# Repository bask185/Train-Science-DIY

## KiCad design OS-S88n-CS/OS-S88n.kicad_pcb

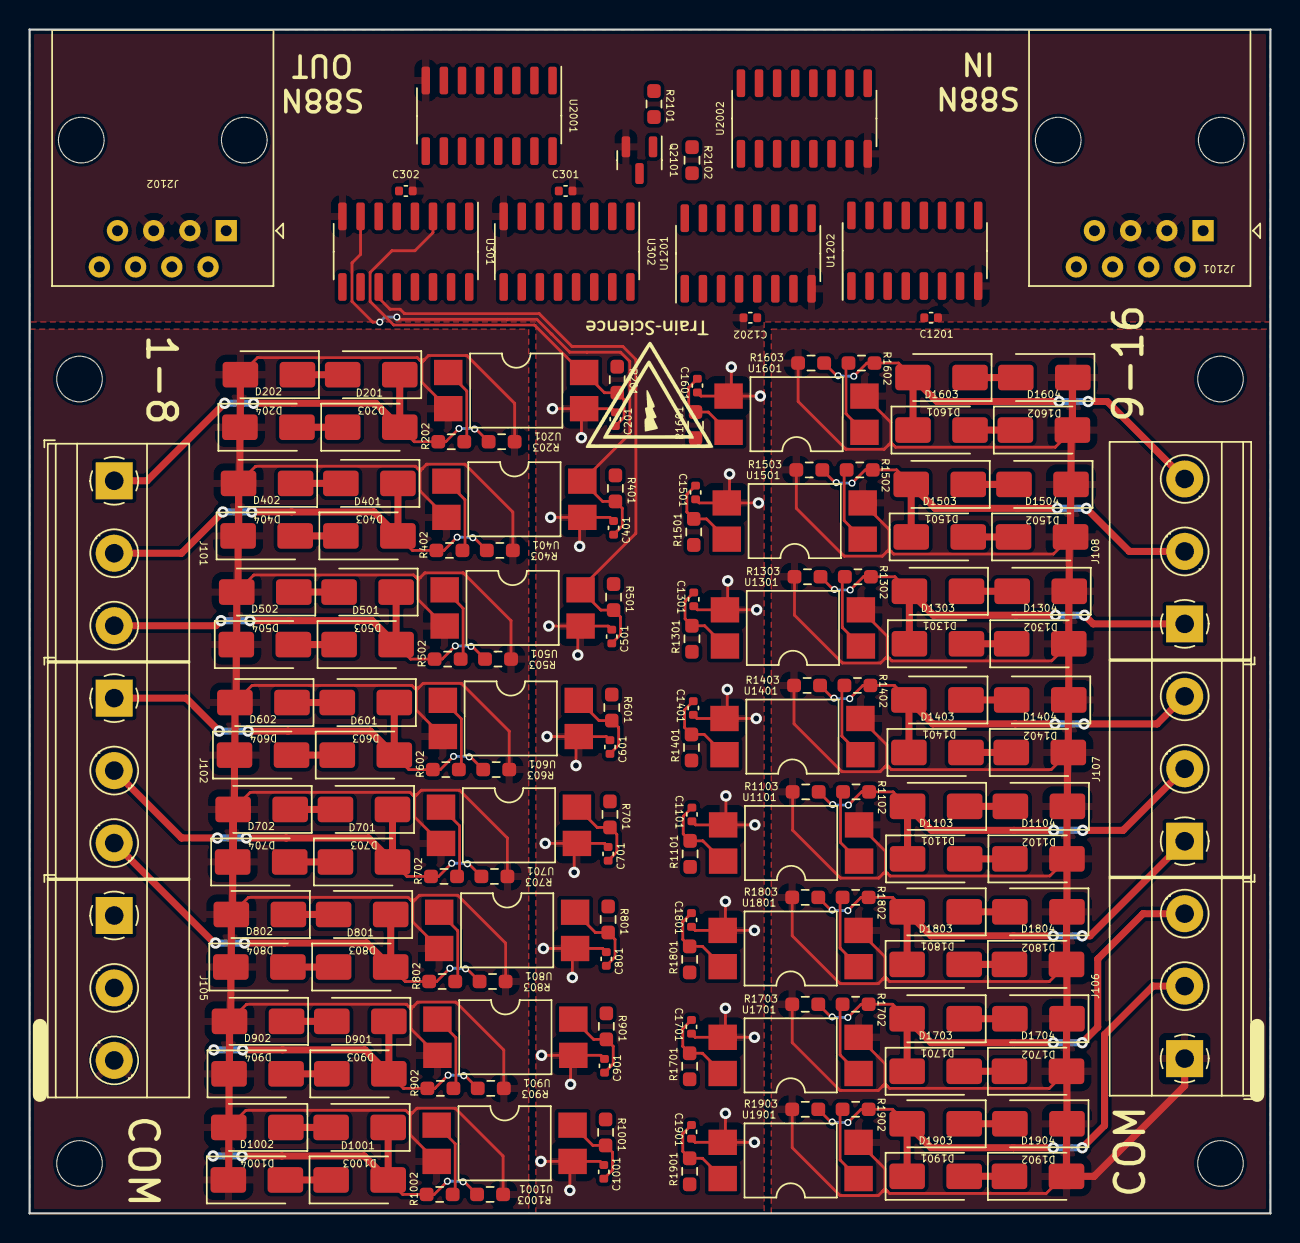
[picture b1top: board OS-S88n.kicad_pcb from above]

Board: 2 copper layers, 87.0 x 83.0 mm, 165 parts (0 on the bottom side), 107 nets.

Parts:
C201, C301, C302, C401, C501, C601, C701, C801, C901, C1001, C1101, C1201, C1202, C1301, C1401, C1501, C1601, C1701, C1801, C1901: 100nF; C_0402_1005Metric
D201, D202, D203, D204, D401, D402, D403, D404, D501, D502, D503, D504, D601, D602, D603, D604, D701, D702, D703, D704, D801, D802, D803, D804, D901, D902, D903, D904, D1001, D1002, D1003, D1004, D1101, D1102, D1103, D1104, D1301, D1302, D1303, D1304, D1401, D1402, D1403, D1404, D1501, D1502, D1503, D1504, D1601, D1602, D1603, D1604, D1701, D1702, D1703, D1704, D1801, D1802, D1803, D1804, D1901, D1902, D1903, D1904: SS53; D_SMA
J101, J102, J105, J106, J107, J108: Screw_Terminal_01x03; TerminalBlock_Phoenix_MKDS-1,5-3-5.08_1x03_P5.08mm_Horizont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
J2101, J2102: RJ45; RJ45_Amphenol_54602-x08_Horizontal
Q2101: BC847; SOT-23
R201, R401, R501, R601, R701, R801, R901, R1001, R1101, R1301, R1401, R1501, R1601, R1701, R1801, R1901: 10k; R_0603_smalltext
R202, R402, R502, R602, R702, R802, R902, R1002, R1102, R1302, R1402, R1502, R1602, R1702, R1802, R1902: 47R; R_0603_smalltext
R203, R403, R503, R603, R703, R803, R903, R1003, R1103, R1303, R1403, R1503, R1603, R1703, R1803, R1903, R2101: 4k7; R_0603_smalltext
R2102: 100k; R_0603_smalltext
U201, U401, U501, U601, U701, U801, U901, U1001, U1101, U1301, U1401, U1501, U1601, U1701, U1801, U1901: EL814; SMDIP-4_W9.53mm
U301, U302, U1201, U1202: SOIC-16_3.9x9.9mm_P1.27mm
U2001, U2002: 4014; SOIC-16_3.9x9.9mm_P1.27mm

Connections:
/CS1/CMOS: C201.1, R201.2, U201.4, U301.3 (S1)
/CS1/TRACK: D201.2 (A), D203.1 (K), J101.1, R202.1, R203.1
/CS2/CMOS: C401.1, R401.2, U301.7 (S2), U401.4
/CS2/TRACK: D401.2 (A), D403.1 (K), J101.2, R402.1, R403.1
/CS3/CMOS: C501.1, R501.2, U301.11 (S3), U501.4
/CS3/TRACK: D501.2 (A), D503.1 (K), J101.3, R502.1, R503.1
/CS4/CMOS: C601.1, R601.2, U301.15 (S4), U601.4
/CS4/TRACK: D601.2 (A), D603.1 (K), J102.1, R602.1, R603.1
/CS5/CMOS: C701.1, R701.2, U302.3 (S1), U701.4
/CS5/TRACK: D701.2 (A), D703.1 (K), J102.2, R702.1, R703.1
/CS6/CMOS: C801.1, R801.2, U302.7 (S2), U801.4
/CS6/TRACK: D801.2 (A), D803.1 (K), J102.3, R802.1, R803.1
/CS7/CMOS: C901.1, R901.2, U302.11 (S3), U901.4
/CS7/TRACK: D901.2 (A), D903.1 (K), J105.1, R902.1, R903.1
/CS8/CMOS: C1001.1, R1001.2, U302.15 (S4), U1001.4
/CS8/TRACK: D1001.2 (A), D1003.1 (K), J105.2, R1002.1, R1003.1
/CS9/CMOS: C1901.1, R1901.2, U1201.3 (S1), U1901.4
/CS9/TRACK: D1901.2 (A), D1903.1 (K), J106.2, R1902.1, R1903.1
/CS10/CMOS: C1701.1, R1701.2, U1201.7 (S2), U1701.4
/CS10/TRACK: D1701.2 (A), D1703.1 (K), J106.3, R1702.1, R1703.1
/CS11/CMOS: C1801.1, R1801.2, U1201.11 (S3), U1801.4
/CS11/TRACK: D1801.2 (A), D1803.1 (K), J107.1, R1802.1, R1803.1
/CS12/CMOS: C1101.1, R1101.2, U1101.4, U1201.15 (S4)
/CS12/TRACK: D1101.2 (A), D1103.1 (K), J107.2, R1102.1, R1103.1
/CS13/CMOS: C1401.1, R1401.2, U1202.3 (S1), U1401.4
/CS13/TRACK: D1401.2 (A), D1403.1 (K), J107.3, R1402.1, R1403.1
/CS14/CMOS: C1301.1, R1301.2, U1202.7 (S2), U1301.4
/CS14/TRACK: D1301.2 (A), D1303.1 (K), J108.1, R1302.1, R1303.1
/CS15/CMOS: C1501.1, R1501.2, U1202.11 (S3), U1501.4
/CS15/TRACK: D1501.2 (A), D1503.1 (K), J108.2, R1502.1, R1503.1
/CS16/CMOS: C1601.1, R1601.2, U1202.15 (S4), U1601.4
/CS16/TRACK: D1601.2 (A), D1603.1 (K), J108.3, R1602.1, R1603.1
/RJ45/CLOCK: J2101.4, J2102.4, U2001.10 (CP), U2002.10 (CP)
/RJ45/DATA_IN: J2101.2, U2001.11 (DS)
/RJ45/DATA_OUT: J2102.2, U2002.3 (Q7)
/RJ45/PL: J2101.6, J2102.6, U2001.9 (PL), U2002.9 (PL)
/RJ45/RESET: Q2101.3 (C), R2102.2, U301.4 (R1), U301.6 (R2), U301.12 (R3), U301.14 (R4), U302.4 (R1), U302.6 (R2), U302.12 (R3), U302.14 (R4), U1201.4 (R1), U1201.6 (R2), U1201.12 (R3), U1201.14 (R4), U1202.4 (R1), U1202.6 (R2), U1202.12 (R3), U1202.14 (R4)
/SR-latch1/Q1: U301.13 (Q1), U2001.7 (P0)
/SR-latch1/Q2: U301.9 (Q2), U2001.6 (P1)
/SR-latch1/Q3: U301.10 (Q3), U2001.5 (P2)
/SR-latch1/Q4: U301.1 (Q4), U2001.4 (P3)
/SR-latch1/Q5: U302.13 (Q1), U2001.13 (P4)
/SR-latch1/Q6: U302.9 (Q2), U2001.14 (P5)
/SR-latch1/Q7: U302.10 (Q3), U2001.15 (P6)
/SR-latch1/Q8: U302.1 (Q4), U2001.1 (P7)
/SR-latch2/Q1: U1201.13 (Q1), U2002.7 (P0)
/SR-latch2/Q2: U1201.9 (Q2), U2002.6 (P1)
/SR-latch2/Q3: U1201.10 (Q3), U2002.5 (P2)
/SR-latch2/Q4: U1201.1 (Q4), U2002.4 (P3)
/SR-latch2/Q5: U1202.13 (Q1), U2002.13 (P4)
/SR-latch2/Q6: U1202.9 (Q2), U2002.14 (P5)
/SR-latch2/Q7: U1202.10 (Q3), U2002.15 (P6)
/SR-latch2/Q8: U1202.1 (Q4), U2002.1 (P7)
COM: D202.1 (K), D204.2 (A), D402.1 (K), D404.2 (A), D502.1 (K), D504.2 (A), D602.1 (K), D604.2 (A), D702.1 (K), D704.2 (A), D802.1 (K), D804.2 (A), D902.1 (K), D904.2 (A), D1002.1 (K), D1004.2 (A), D1102.1 (K), D1104.2 (A), D1302.1 (K), D1304.2 (A), D1402.1 (K), D1404.2 (A), D1502.1 (K), D1504.2 (A), D1602.1 (K), D1604.2 (A), D1702.1 (K), D1704.2 (A), D1802.1 (K), D1804.2 (A), D1902.1 (K), D1904.2 (A), J105.3, J106.1, R203.2, R403.2, R503.2, R603.2, R703.2, R803.2, R903.2, R1003.2, R1103.2, R1303.2, R1403.2, R1503.2, R1603.2, R1703.2, R1803.2, R1903.2, U201.2, U401.2, U501.2, U601.2, U701.2, U801.2, U901.2, U1001.2, U1101.2, U1301.2, U1401.2, U1501.2, U1601.2, U1701.2, U1801.2, U1901.2
GND: C201.2, C301.2, C302.2, C401.2, C501.2, C601.2, C701.2, C801.2, C901.2, C1001.2, C1101.2, C1201.2, C1202.2, C1301.2, C1401.2, C1501.2, C1601.2, C1701.2, C1801.2, C1901.2, J2101.3, J2101.5, J2102.3, J2102.5, Q2101.2 (E), U201.3, U301.8 (GND), U302.8 (GND), U401.3, U501.3, U601.3, U701.3, U801.3, U901.3, U1001.3, U1101.3, U1201.8 (GND), U1202.8 (GND), U1301.3, U1401.3, U1501.3, U1601.3, U1701.3, U1801.3, U1901.3, U2001.8 (Vss), U2002.8 (Vss)
unnamed: D201.1 (K), D202.2 (A)
unnamed: D203.2 (A), D204.1 (K)
unnamed: D401.1 (K), D402.2 (A)
unnamed: D403.2 (A), D404.1 (K)
unnamed: D501.1 (K), D502.2 (A)
unnamed: D503.2 (A), D504.1 (K)
unnamed: D601.1 (K), D602.2 (A)
unnamed: D603.2 (A), D604.1 (K)
unnamed: D701.1 (K), D702.2 (A)
unnamed: D703.2 (A), D704.1 (K)
unnamed: D801.1 (K), D802.2 (A)
unnamed: D803.2 (A), D804.1 (K)
unnamed: D901.1 (K), D902.2 (A)
unnamed: D903.2 (A), D904.1 (K)
unnamed: D1001.1 (K), D1002.2 (A)
unnamed: D1003.2 (A), D1004.1 (K)
unnamed: D1101.1 (K), D1102.2 (A)
unnamed: D1103.2 (A), D1104.1 (K)
unnamed: D1301.1 (K), D1302.2 (A)
unnamed: D1303.2 (A), D1304.1 (K)
unnamed: D1401.1 (K), D1402.2 (A)
unnamed: D1403.2 (A), D1404.1 (K)
unnamed: D1501.1 (K), D1502.2 (A)
unnamed: D1503.2 (A), D1504.1 (K)
unnamed: D1601.1 (K), D1602.2 (A)
unnamed: D1603.2 (A), D1604.1 (K)
unnamed: D1701.1 (K), D1702.2 (A)
unnamed: D1703.2 (A), D1704.1 (K)
unnamed: D1801.1 (K), D1802.2 (A)
unnamed: D1803.2 (A), D1804.1 (K)
unnamed: D1901.1 (K), D1902.2 (A)
unnamed: D1903.2 (A), D1904.1 (K)
unnamed: J2101.7, J2102.7, R2101.1
unnamed: Q2101.1 (B), R2101.2
unnamed: R202.2, U201.1
unnamed: R402.2, U401.1
unnamed: R502.2, U501.1
unnamed: R602.2, U601.1
unnamed: R702.2, U701.1
unnamed: R802.2, U801.1
unnamed: R902.2, U901.1
unnamed: R1002.2, U1001.1
unnamed: R1102.2, U1101.1
unnamed: R1302.2, U1301.1
unnamed: R1402.2, U1401.1
unnamed: R1502.2, U1501.1
unnamed: R1602.2, U1601.1
unnamed: R1702.2, U1701.1
unnamed: R1802.2, U1801.1
unnamed: R1902.2, U1901.1
unnamed: U2001.3 (Q7), U2002.11 (DS)
VCC: C301.1, C302.1, C1201.1, C1202.1, J2101.1, J2102.1, R201.1, R401.1, R501.1, R601.1, R701.1, R801.1, R901.1, R1001.1, R1101.1, R1301.1, R1401.1, R1501.1, R1601.1, R1701.1, R1801.1, R1901.1, R2102.1, U301.5 (enable), U302.5 (enable), U1201.5 (enable), U1202.5 (enable), U2001.16 (Vdd), U2002.16 (Vdd)

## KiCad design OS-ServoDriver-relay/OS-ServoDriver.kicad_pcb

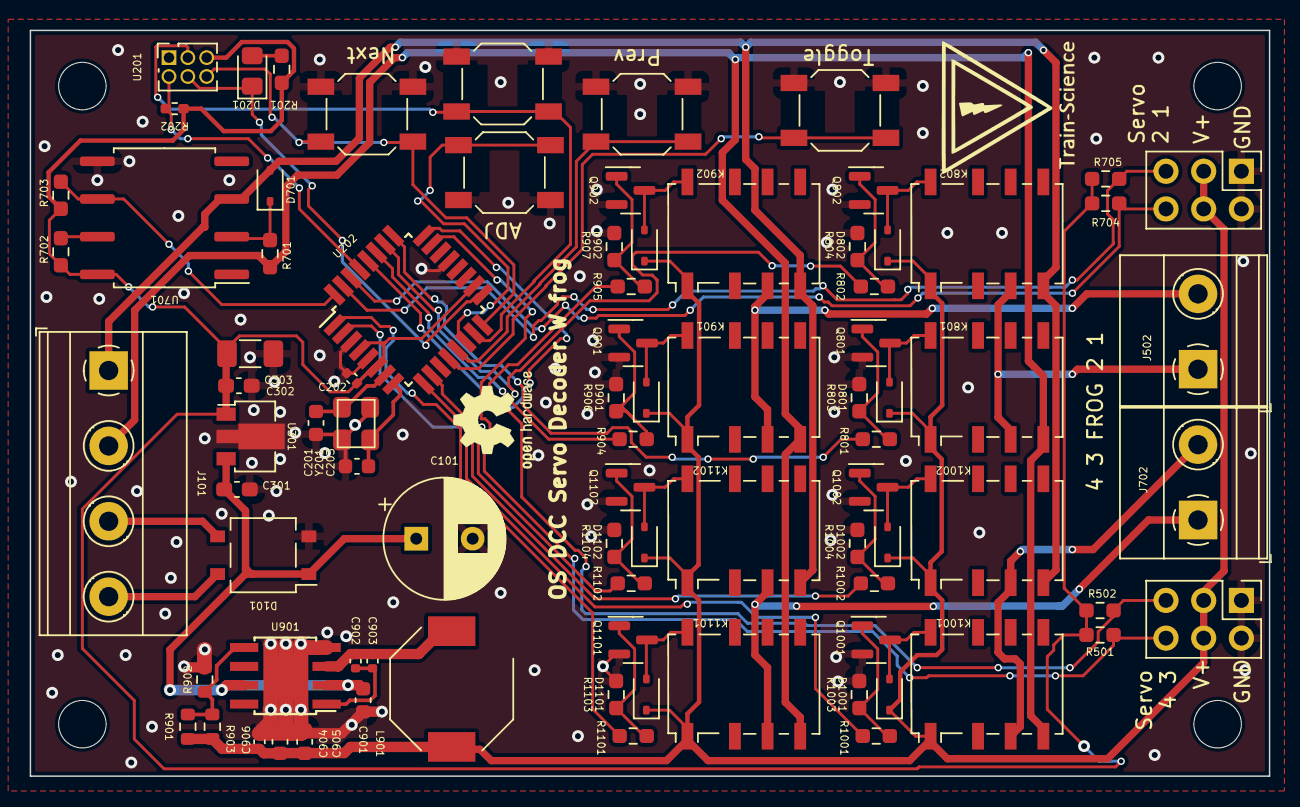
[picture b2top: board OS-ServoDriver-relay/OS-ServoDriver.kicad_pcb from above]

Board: 2 copper layers, 83.5 x 50.2 mm, 85 parts (0 on the bottom side), 56 nets.

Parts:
C101: 100uF; CP_Radial_D8.0mm_P3.80mm
C201, C203: 12pF; C_0603_1608Metric
C202, C902, C906: 100nF; C_0402_1005Metric
C301: 330nF; C_0603_1608Metric_Pad1.08x0.95mm_HandSolder
C302: 100nF; C_0603_1608Metric_Pad1.08x0.95mm_HandSolder
C303: 100uF; C_1206_3216Metric_Pad1.33x1.80mm_HandSolder
C901, C904, C905: 22uF; C_0603_1608Metric
C903: 22nF; C_0402_1005Metric
D101: MB10S; TO-269AA
D201: LED; LED_0805_2012Metric_Pad1.15x1.40mm_HandSolder
D701, D801, D802, D901, D902, D1001, D1002, D1101, D1102: 1N4148WS; D_SOD-323
J101: Screw_Terminal_01x04; TerminalBlock_Phoenix_MKDS-1,5-4-5.08_1x04_P5.08mm_Horizont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
J501, J701: Servo; PinHeader_2x03_P2.54mm_Vertical
J502, J702: Frogs; TerminalBlock_Phoenix_MKDS-1,5-2-5.08_1x02_P5.08mm_Horizont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
K801, K802, K901, K902, K1001, K1002, K1101, K1102: G6K-2F-Y-TR DC5; Relay_DPDT_Omron_G6K-2F-Y
L901: L; L_Bourns-SRU8028_8.0x8.0mm
Q801, Q802, Q901, Q902, Q1001, Q1002, Q1101, Q1102: AO3400A; SOT-23
R201: 6k2; R_0603_1608Metric_Pad0.98x0.95mm_HandSolder
R202: 10k; R_0402_1005Metric_Pad0.72x0.64mm_HandSolder
R501, R502, R702, R703, R704, R705, R803, R804, R906, R907, R1003, R1004, R1103, R1104: 10k; R_0603_smalltext
R701: 1k5; R_0603_smalltext
R801, R802, R904, R905, R1001, R1002, R1101, R1102: 22R; R_0603_smalltext
R901: 220k; R_0603_1608Metric
R902: 20k; R_0603_1608Metric
R903: 150k; R_0603_1608Metric
SW101, SW102, SW103, SW104, SW105: default_switch
U201: HEADER_3x2; PinSocket_2x03_P1.27mm_Vertical
U202: ATmega328-A; TQFP-32_7x7mm_P0.8mm
U301: L78L05_SOT89; SOT-89-3
U701: 6N137; SOP-8_6.62x9.15mm_P2.54mm
U901: MT2499A; TI_SO-PowerPAD-8
Y201: Crystal_GND2; crystal_arduino

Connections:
+5V: C202.1, C302.1, C303.1, R201.1, R202.1, R501.1, R502.1, R702.1, R703.1, R704.1, R705.1, U201.5, U202.4 (VCC), U202.6 (VCC), U202.18 (AVCC), U301.1 (OUT), U701.8 (VCC)
+5VA: C904.1, C905.1, C906.1, D801.1 (K), D802.1 (K), D901.1 (K), D902.1 (K), D1001.1 (K), D1002.1 (K), D1101.1 (K), D1102.1 (K), J501.3, J501.4, J701.3, J701.4, K801.1, K802.1, K901.1, K902.1, K1001.1, K1002.1, K1101.1, K1102.1, L901.2, R901.1, R903.2
/DCC/DCC_TTL: R703.2, U202.32 (PD2), U701.6 (VO)
/DCC_A: J101.2, K801.4, K901.4, K1001.4, K1101.4, R701.1
/DCC_B: D701.2 (A), J101.1, K802.4, K902.4, K1002.4, K1102.4, U701.3 (C)
/Servo1-2/Frog1: J502.1, K801.3, K802.3
/Servo1-2/Frog2: J502.2, K901.3, K902.3
/Servo1-2/Relay1: R801.1, U202.25 (PC2)
/Servo1-2/Relay2: R802.1, U202.26 (PC3)
/Servo1-2/Relay3: R904.1, U202.27 (PC4)
/Servo1-2/Relay4: R905.1, U202.28 (PC5)
/Servo1-2/Servo1: J501.6, R501.2, U202.23 (PC0)
/Servo1-2/Servo2: J501.5, R502.2, U202.24 (PC1)
/Servo3-4/Frog1: J702.1, K1101.3, K1102.3
/Servo3-4/Frog2: J702.2, K1001.3, K1002.3
/Servo3-4/Relay1: R1101.1, U202.1 (PD3)
/Servo3-4/Relay2: R1102.1, U202.2 (PD4)
/Servo3-4/Relay3: R1001.1, U202.9 (PD5)
/Servo3-4/Relay4: R1002.1, U202.10 (PD6)
/Servo3-4/Servo1: J701.6, R704.2, U202.30 (PD0)
/Servo3-4/Servo2: J701.5, R705.2, U202.31 (PD1)
/atmega/D8: SW105.2 (B), U202.12 (PB0)
/atmega/D9: SW104.2 (B), U202.13 (PB1)
/atmega/D10: SW103.2 (B), U202.14 (PB2)
/atmega/LED: D201.1 (K), U201.4, U202.17 (PB5)
/atmega/MISO: SW101.2 (B), U201.6, U202.16 (PB4)
/atmega/MOSI: SW102.2 (B), U201.3, U202.15 (PB3)
/atmega/X1: C201.2, U202.7 (XTAL1/PB6), Y201.1
/atmega/X2: C203.2, U202.8 (XTAL2/PB7), Y201.3
/atmega/reset: R202.2, U201.2, U202.29 (~RESET/PC6)
GND: C101.2, C201.1, C202.2, C203.1, C301.2, C302.2, C303.2, C901.2, C904.2, C905.2, C906.2, D101.2 (-), J501.1, J501.2, J701.1, J701.2, Q801.2 (S), Q802.2 (S), Q901.2 (S), Q902.2 (S), Q1001.2 (S), Q1002.2 (S), Q1101.2 (S), Q1102.2 (S), R803.1, R804.1, R902.2, R906.1, R907.1, R1003.1, R1004.1, R1103.1, R1104.1, SW101.1 (A), SW102.1 (A), SW103.1 (A), SW104.1 (A), SW105.1 (A), U201.1, U202.3 (GND), U202.5 (GND), U202.21 (GND), U301.2 (GND), U701.5 (GND), U901.4 (GND), U901.9 (GND), Y201.2 (GND), Y201.4 (GND)
unnamed: D201.2 (A), R201.2
unnamed: D701.1 (K), R701.2, U701.2 (A)
unnamed: D801.2 (A), K801.8, Q801.3 (D)
unnamed: D802.2 (A), K802.8, Q802.3 (D)
unnamed: D901.2 (A), K901.8, Q901.3 (D)
unnamed: D902.2 (A), K902.8, Q902.3 (D)
unnamed: D1001.2 (A), K1001.8, Q1001.3 (D)
unnamed: D1002.2 (A), K1002.8, Q1002.3 (D)
unnamed: D1101.2 (A), K1101.8, Q1101.3 (D)
unnamed: D1102.2 (A), K1102.8, Q1102.3 (D)
unnamed: D101.3, J101.3
unnamed: D101.4, J101.4
unnamed: Q801.1 (G), R801.2, R803.2
unnamed: Q802.1 (G), R802.2, R804.2
unnamed: Q901.1 (G), R904.2, R906.2
unnamed: Q902.1 (G), R905.2, R907.2
unnamed: Q1001.1 (G), R1001.2, R1003.2
unnamed: Q1002.1 (G), R1002.2, R1004.2
unnamed: Q1101.1 (G), R1101.2, R1103.2
unnamed: Q1102.1 (G), R1102.2, R1104.2
unnamed: R702.2, U701.7 (EN)
unnamed: C902.1, C903.1, U901.1 (BS)
unnamed: R901.2, R902.1, R903.1, U901.5 (FB)
unnamed: C902.2, C903.2, L901.1, U901.3 (SW)
VCC: C101.1, C301.1, C901.1, D101.1 (+), U301.3 (IN), U901.2 (Vin), U901.7 (EN)

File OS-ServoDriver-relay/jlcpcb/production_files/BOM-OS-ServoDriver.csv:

Comment,Designator,Footprint,LCSC
6N137,U701,SOP-8_6.62x9.15mm_P2.54mm,C110020
Crystal_GND2,Y201,crystal_arduino,C13738
100nF,C302,C_0603_1608Metric_Pad1.08x0.95mm_HandSolder,C14663
ATmega328-A,U202,TQFP-32_7x7mm_P0.8mm,C14877
100uF,C303,C_1206_3216Metric_Pad1.33x1.80mm_HandSolder,C15008
330nF,C301,C_0603_1608Metric_Pad1.08x0.95mm_HandSolder,C1615
22nF,C903,C_0402_1005Metric,C1729
AO3400A,"Q1001,Q1002,Q1101,Q1102,Q801,Q802,Q901,Q902",SOT-23,C20917
1N4148WS,"D1001,D1002,D1101,D1102,D701,D801,D802,D901,D902",D_SOD-323,C2128
150k,R903,R_0603_1608Metric,C22807
1k5,R701,R_0603_smalltext,C22843
220k,R901,R_0603_1608Metric,C22961
22R,"R1001,R1002,R1101,R1102,R801,R802,R904,R905",R_0603_smalltext,C23345
MB10S,D101,TO-269AA,C2488
10k,R202,R_0402_1005Metric_Pad0.72x0.64mm_HandSolder,C25744
10k,"R1003,R1004,R1103,R1104,R501,R502,R702,R703,R704,R705,R803,R804,R906,R907",R_0603_smalltext,C25804
L,L901,L_Bourns-SRU8028_8.0x8.0mm,C2929438
MT2499A,U901,TI_SO-PowerPAD-8,C3007555
100nF,"C202,C902,C906",C_0402_1005Metric,C307331
default_switch,"SW101,SW102,SW103,SW104,SW105",default_switch,C318884
12pF,"C201,C203",C_0603_1608Metric,C38523
6k2,R201,R_0603_1608Metric_Pad0.98x0.95mm_HandSolder,C4260
20k,R902,R_0603_1608Metric,C4328
22uF,"C901,C904,C905",C_0603_1608Metric,C45783
G6K-2F-Y-TR DC5,"K1001,K1002,K1101,K1102,K801,K802,K901,K902",Relay_DPDT_Omron_G6K-2F-Y,C47190
Servo,"J501,J701",PinHeader_2x03_P2.54mm_Vertical,C65114
L78L05_SOT89,U301,SOT-89-3,C71136
LED,D201,LED_0805_2012Metric_Pad1.15x1.40mm_HandSolder,C84256

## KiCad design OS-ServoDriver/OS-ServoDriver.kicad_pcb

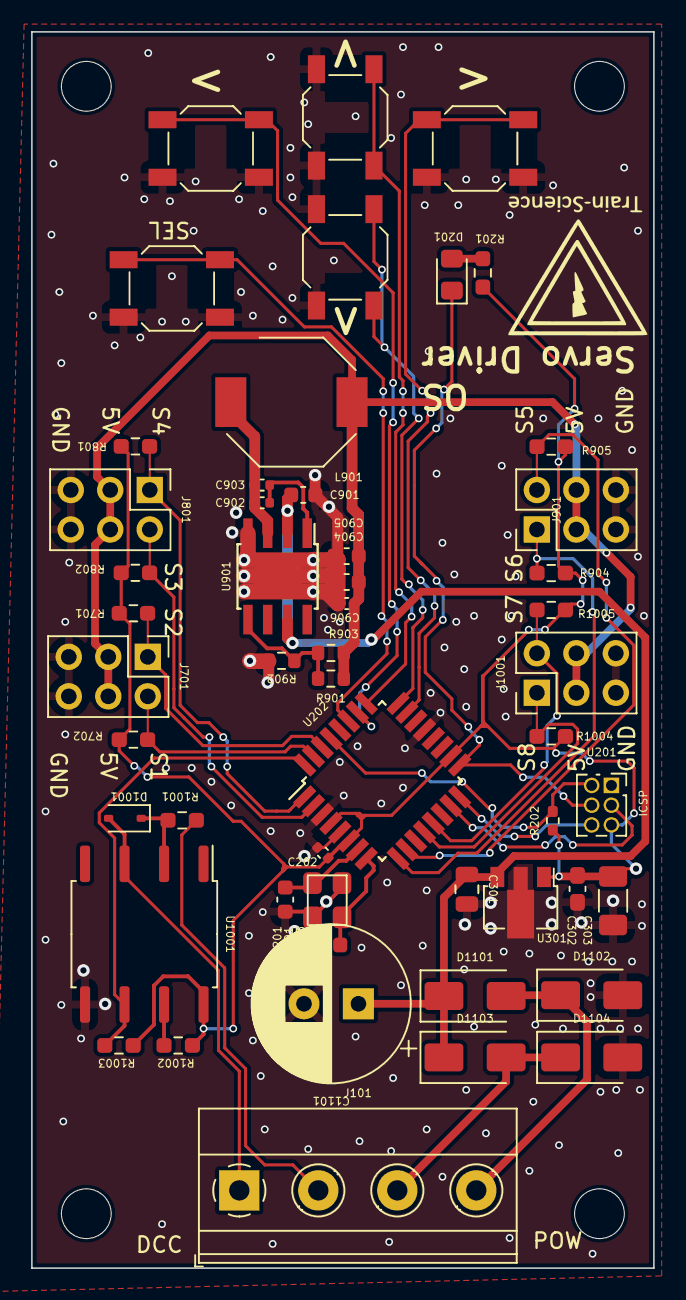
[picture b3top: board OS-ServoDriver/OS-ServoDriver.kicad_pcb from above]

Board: 2 copper layers, 40.0 x 79.5 mm, 52 parts (0 on the bottom side), 34 nets.

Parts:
C201, C203: 12pF; C_0603_1608Metric
C202, C902, C906: 100nF; C_0402_1005Metric
C301: 470nF; C_0805_2012Metric
C302: 100nF; C_0603_1608Metric_Pad1.08x0.95mm_HandSolder
C303: 100uF; C_1206_3216Metric_Pad1.33x1.80mm_HandSolder
C901, C904, C905: 22uF; C_0603_1608Metric
C903: 22nF; C_0402_1005Metric
C1101: 1000uF; CP_Radial_D10.0mm_P3.50mm
D201: LED; LED_0805_2012Metric_Pad1.15x1.40mm_HandSolder
D1001: 1N4148WS; D_SOD-323
D1101, D1102, D1103, D1104: SS53; D_SMA
J101: Screw_Terminal_01x04; TerminalBlock_Phoenix_MKDS-1,5-4-5.08_1x04_P5.08mm_Horizont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
J701, J801, J901, J1001: Conn_02x03_Odd_Even; PinHeader_2x03_P2.54mm_Vertical
L901: L; L_Bourns-SRU8028_8.0x8.0mm
R201: 6k2; R_0603_1608Metric_Pad0.98x0.95mm_HandSolder
R202: 10k; R_0402_1005Metric_Pad0.72x0.64mm_HandSolder
R701, R702, R801, R802, R904, R905, R1002, R1003, R1004, R1005: 10k; R_0603_smalltext
R901: 220k; R_0603_1608Metric
R902: 20k; R_0603_1608Metric
R903: 150k; R_0603_1608Metric
R1001: 1k; R_0603_smalltext
SW601, SW602, SW603, SW604, SW605: default_switch
U201: HEADER_3x2; PinSocket_2x03_P1.27mm_Vertical
U202: ATmega328-A; TQFP-32_7x7mm_P0.8mm
U301: L78L05_SOT89; SOT-89-3
U901: MT2499A; TI_SO-PowerPAD-8
U1001: 6N137; SOP-8_6.62x9.15mm_P2.54mm
Y201: Crystal_GND2; crystal_arduino

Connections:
+5V: C202.1, C302.1, C303.1, R201.1, R202.1, R701.2, R702.2, R801.2, R802.2, R904.2, R905.2, R1002.1, R1003.1, R1004.2, R1005.2, U201.5, U202.4 (VCC), U202.6 (VCC), U202.18 (AVCC), U301.1 (OUT), U1001.8 (VCC)
+5VA: C904.1, C905.1, C906.1, J701.3, J701.4, J801.3, J801.4, J901.3, J901.4, J1001.3, J1001.4, L901.2, R901.1, R903.2
/DCC/DCC_A: J101.2, R1001.1
/DCC/DCC_B: D1001.2 (A), J101.1, U1001.3 (C)
/DCC/DCC_TTL: R1003.2, U202.32 (PD2), U1001.6 (VO)
/D_bridge/AC_1: D1101.2 (A), D1102.1 (K), J101.4
/D_bridge/AC_2: D1103.2 (A), D1104.1 (K), J101.3
/atmega/LED: D201.1 (K), U201.4, U202.17 (PB5)
/atmega/MISO: U201.6, U202.16 (PB4)
/atmega/MOSI: U201.3, U202.15 (PB3)
/atmega/X1: C201.2, U202.7 (XTAL1/PB6), Y201.1
/atmega/X2: C203.2, U202.8 (XTAL2/PB7), Y201.3
/atmega/bus1.pin1: J701.1, R701.1, U202.30 (PD0)
/atmega/bus1.pin2: J701.2, R702.1, U202.31 (PD1)
/atmega/bus2.pin1: J801.1, R801.1, U202.1 (PD3)
/atmega/bus2.pin2: J801.2, R802.1, U202.2 (PD4)
/atmega/bus3.pin1: J901.1, R904.1, U202.9 (PD5)
/atmega/bus3.pin2: J901.2, R905.1, U202.10 (PD6)
/atmega/bus4.pin1: J1001.1, R1004.1, U202.12 (PB0)
/atmega/bus4.pin2: J1001.2, R1005.1, U202.13 (PB1)
/atmega/reset: R202.2, U201.2, U202.29 (~RESET/PC6)
/atmega/sw1: SW601.2 (B), U202.23 (PC0)
/atmega/sw2: SW602.2 (B), U202.24 (PC1)
/atmega/sw3: SW603.2 (B), U202.25 (PC2)
/atmega/sw4: SW604.2 (B), U202.26 (PC3)
/atmega/sw5: SW605.2 (B), U202.27 (PC4)
GND: C201.1, C202.2, C203.1, C301.2, C302.2, C303.2, C901.2, C904.2, C905.2, C906.2, C1101.2, D1102.2 (A), D1104.2 (A), J701.5, J701.6, J801.5, J801.6, J901.5, J901.6, J1001.5, J1001.6, R902.2, SW601.1 (A), SW602.1 (A), SW603.1 (A), SW604.1 (A), SW605.1 (A), U201.1, U202.3 (GND), U202.5 (GND), U202.21 (GND), U301.2 (GND), U901.4 (GND), U901.9 (GND), U1001.5 (GND), Y201.2 (GND), Y201.4 (GND)
unnamed: D201.2 (A), R201.2
unnamed: D1001.1 (K), R1001.2, U1001.2 (A)
unnamed: C902.1, C903.1, U901.1 (BS)
unnamed: R901.2, R902.1, R903.1, U901.5 (FB)
unnamed: C902.2, C903.2, L901.1, U901.3 (SW)
unnamed: R1002.2, U1001.7 (EN)
VCC: C301.1, C901.1, C1101.1, D1101.1 (K), D1103.1 (K), U301.3 (IN), U901.2 (Vin), U901.7 (EN)

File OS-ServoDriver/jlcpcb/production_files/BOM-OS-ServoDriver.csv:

Comment,Designator,Footprint,LCSC
6N137,U1001,SOP-8_6.62x9.15mm_P2.54mm,C110020
Crystal_GND2,Y201,crystal_arduino,C13738
470nF,C301,C_0805_2012Metric,C13967
100nF,C302,C_0603_1608Metric_Pad1.08x0.95mm_HandSolder,C14663
ATmega328-A,U202,TQFP-32_7x7mm_P0.8mm,C14877
100uF,C303,C_1206_3216Metric_Pad1.33x1.80mm_HandSolder,C15008
22nF,C903,C_0402_1005Metric,C1729
1k,R1001,R_0603_smalltext,C21190
1N4148WS,D1001,D_SOD-323,C2128
150k,R903,R_0603_1608Metric,C22807
220k,R901,R_0603_1608Metric,C22961
10k,R202,R_0402_1005Metric_Pad0.72x0.64mm_HandSolder,C25744
10k,"R1002,R1003,R1004,R1005,R701,R702,R801,R802,R904,R905",R_0603_smalltext,C25804
L,L901,L_Bourns-SRU8028_8.0x8.0mm,C2929438
MT2499A,U901,TI_SO-PowerPAD-8,C3007555
100nF,"C202,C902,C906",C_0402_1005Metric,C307331
default_switch,"SW601,SW602,SW603,SW604,SW605",default_switch,C318884
12pF,"C201,C203",C_0603_1608Metric,C38523
6k2,R201,R_0603_1608Metric_Pad0.98x0.95mm_HandSolder,C4260
20k,R902,R_0603_1608Metric,C4328
22uF,"C901,C904,C905",C_0603_1608Metric,C45783
Conn_02x03_Odd_Even,"J1001,J701,J801,J901",PinHeader_2x03_P2.54mm_Vertical,C65114
L78L05_SOT89,U301,SOT-89-3,C71136
LED,D201,LED_0805_2012Metric_Pad1.15x1.40mm_HandSolder,C84256
SS53,"D1101,D1102,D1103,D1104",D_SMA,C8678
Screw_Terminal_01x04,J101,"TerminalBlock_Phoenix_MKDS-1,5-4-5.08_1x04_P5.08mm_Horizontal",
1000uF,C1101,CP_Radial_D10.0mm_P3.50mm,

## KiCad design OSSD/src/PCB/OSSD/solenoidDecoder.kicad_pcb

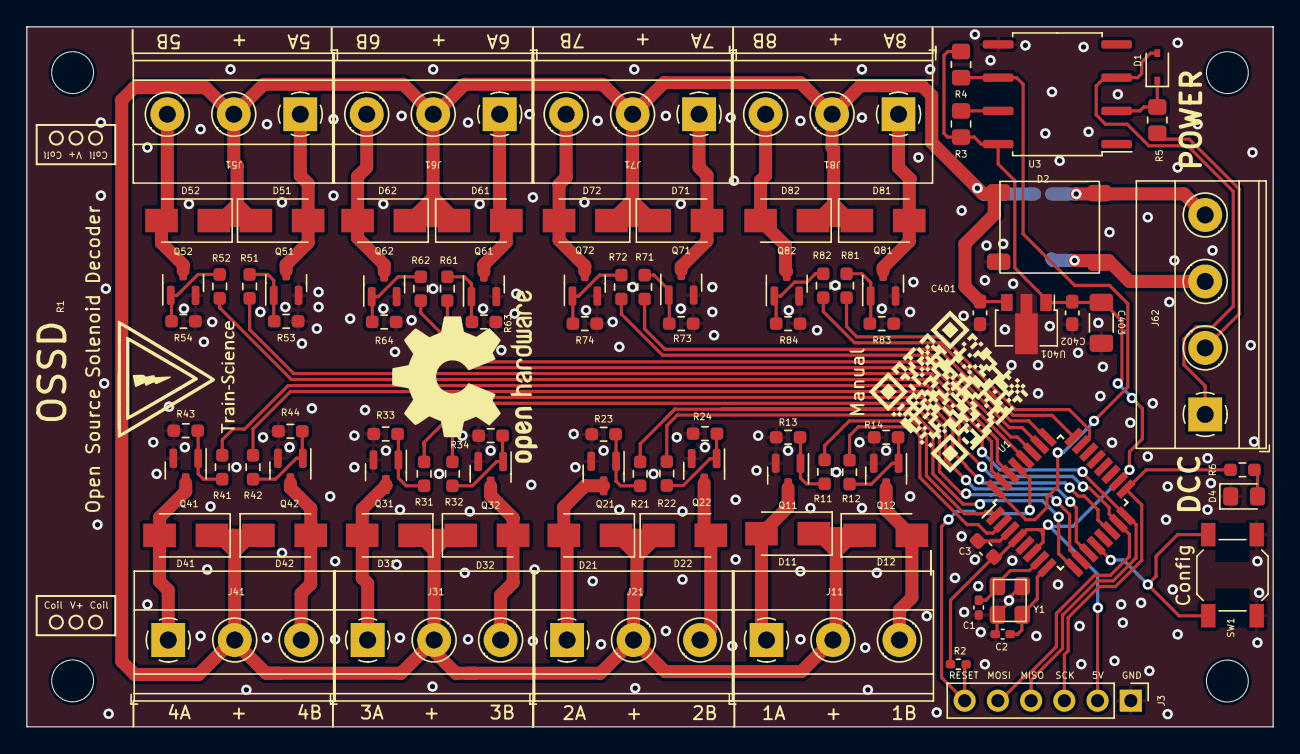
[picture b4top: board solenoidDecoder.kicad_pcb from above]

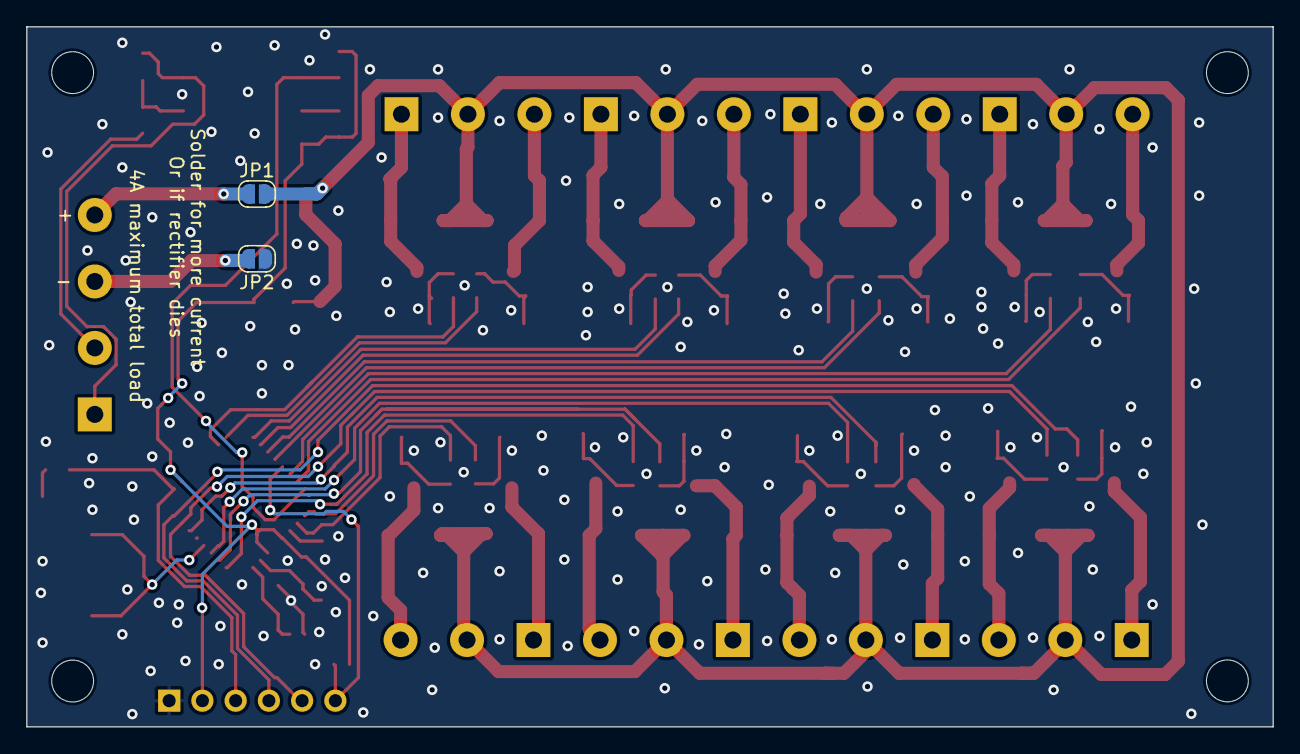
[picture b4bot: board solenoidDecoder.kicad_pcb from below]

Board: 2 copper layers, 95.3 x 53.5 mm, 95 parts (2 on the bottom side), 64 nets.

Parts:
C1, C2: 12pF; C_0402_1005Metric_Pad0.74x0.62mm_HandSolder
C3, C402: 100nF; C_0603_1608Metric_Pad1.08x0.95mm_HandSolder
C401: 330nF; C_0603_1608Metric_Pad1.08x0.95mm_HandSolder
C403: 100uF; C_1206_3216Metric_Pad1.33x1.80mm_HandSolder
D1: D; D_SOD-323
D2: 4A rectifier
D4: LED; LED_0805_2012Metric_Pad1.15x1.40mm_HandSolder
D11, D12, D21, D22, D31, D32, D41, D42, D51, D52, D61, D62, D71, D72, D81, D82: D_SMA
J3: ICSP; PinHeader_1x06_P2.54mm_Vertical
J11, J21, J31, J41, J51, J61, J71, J81: TerminalBlock_Phoenix_MKDS-1,5-3-5.08_1x03_P5.08mm_Horizont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
J62: Screw_Terminal_01x04; TerminalBlock_Phoenix_MKDS-1,5-4-5.08_1x04_P5.08mm_Horizont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
JP1, JP2: SolderJumper_2_Open; SolderJumper-2_P1.3mm_Open_RoundedPad1.0x1.5mm
Q11, Q12, Q21, Q22, Q31, Q32, Q41, Q42, Q51, Q52, Q61, Q62, Q71, Q72, Q81, Q82: SOT-23
R2: 10k; R_0402_1005Metric_Pad0.72x0.64mm_HandSolder
R3, R4: 10k; R_0805_2012Metric_Pad1.20x1.40mm_HandSolder
R5: 1k; R_0805_2012Metric_Pad1.20x1.40mm_HandSolder
R6: 6k2; R_0603_1608Metric_Pad0.98x0.95mm_HandSolder
R11, R12, R13, R14, R21, R22, R23, R24, R31, R32, R33, R34, R41, R42, R43, R44, R51, R52, R53, R54, R61, R62, R63, R64, R71, R72, R73, R74, R81, R82, R83, R84: R_0603_1608Metric_Pad0.98x0.95mm_HandSolder
SW1: SW_SPST; SW_SPST_SKQG_WithStem
U1: ATmega328-A; TQFP-32_7x7mm_P0.8mm
U3: 6N137; SOP-8_6.62x9.15mm_P2.54mm
U401: L78L05_SOT89; SOT-89-3
Y1: Crystal_GND2; crystal_arduino

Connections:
+5V: C3.2, C402.1, C403.1, J3.2, R2.1, R3.1, R4.1, U1.4 (VCC), U1.6 (VCC), U1.18 (AVCC), U3.8 (VCC), U401.1 (OUT)
/DCC/DCC_A: J62.2, R5.1
/DCC/DCC_B: D1.2 (A), J62.1, U3.3 (C)
/DCC/DCC_TTL: R4.2, U1.32 (PD2), U3.6 (VO)
/POWER/Vcoils: C401.1, D2.1 (+), D11.1 (K), D12.1 (K), D21.1 (K), D22.1 (K), D31.1 (K), D32.1 (K), D41.1 (K), D42.1 (K), D51.1 (K), D52.1 (K), D61.1 (K), D62.1 (K), D71.1 (K), D72.1 (K), D81.1 (K), D82.1 (K), J11.2, J21.2, J31.2, J41.2, J51.2, J61.2, J71.2, J81.2, JP1.2 (B), U401.3 (IN)
/POWER/Vin1: D2.4, J62.4, JP1.1 (A)
/POWER/Vin2: D2.3, J62.3, JP2.2 (B)
/uController/GPIO1: R12.1, U1.2 (PD4)
/uController/GPIO2: R11.1, U1.1 (PD3)
/uController/GPIO3: R22.1, U1.9 (PD5)
/uController/GPIO4: R21.1, U1.10 (PD6)
/uController/GPIO5: R32.1, U1.11 (PD7)
/uController/GPIO6: R31.1, U1.14 (PB2)
/uController/GPIO7: J3.5, R42.1, U1.15 (PB3)
/uController/GPIO8: J3.4, R41.1, U1.16 (PB4)
/uController/GPIO9: R52.1, U1.31 (PD1)
/uController/GPIO10: R51.1, U1.30 (PD0)
/uController/GPIO11: R62.1, U1.28 (PC5)
/uController/GPIO12: R61.1, U1.27 (PC4)
/uController/GPIO13: R72.1, U1.26 (PC3)
/uController/GPIO14: R71.1, U1.25 (PC2)
/uController/GPIO15: R82.1, U1.24 (PC1)
/uController/GPIO16: R81.1, U1.23 (PC0)
/uController/LED: J3.3, R6.1, U1.17 (PB5)
/uController/RESET: J3.6, R2.2, U1.29 (~RESET/PC6)
/uController/X1: C1.2, U1.7 (XTAL1/PB6), Y1.1
/uController/X2: C2.2, U1.8 (XTAL2/PB7), Y1.3
GND: C1.1, C2.1, C3.1, C401.2, C402.2, C403.2, D2.2 (-), D4.1 (K), J3.1, JP2.1 (A), Q11.2 (S), Q12.2 (S), Q21.2 (S), Q22.2 (S), Q31.2 (S), Q32.2 (S), Q41.2 (S), Q42.2 (S), Q51.2 (S), Q52.2 (S), Q61.2 (S), Q62.2 (S), Q71.2 (S), Q72.2 (S), Q81.2 (S), Q82.2 (S), R13.1, R14.1, R23.1, R24.1, R33.1, R34.1, R43.1, R44.1, R53.1, R54.1, R63.1, R64.1, R73.1, R74.1, R83.1, R84.1, SW1.2 (B), U1.3 (GND), U1.5 (GND), U1.21 (GND), U3.5 (GND), U401.2 (GND), Y1.2 (GND), Y1.4 (GND)
unnamed: D1.1 (K), R5.2, U3.2 (A)
unnamed: D4.2 (A), R6.2
unnamed: D11.2 (A), J11.1, Q11.3 (D)
unnamed: D12.2 (A), J11.3, Q12.3 (D)
unnamed: D21.2 (A), J21.1, Q21.3 (D)
unnamed: D22.2 (A), J21.3, Q22.3 (D)
unnamed: D31.2 (A), J31.1, Q31.3 (D)
unnamed: D32.2 (A), J31.3, Q32.3 (D)
unnamed: D41.2 (A), J41.1, Q41.3 (D)
unnamed: D42.2 (A), J41.3, Q42.3 (D)
unnamed: D51.2 (A), J51.1, Q51.3 (D)
unnamed: D52.2 (A), J51.3, Q52.3 (D)
unnamed: D61.2 (A), J61.1, Q61.3 (D)
unnamed: D62.2 (A), J61.3, Q62.3 (D)
unnamed: D71.2 (A), J71.1, Q71.3 (D)
unnamed: D72.2 (A), J71.3, Q72.3 (D)
unnamed: D81.2 (A), J81.1, Q81.3 (D)
unnamed: D82.2 (A), J81.3, Q82.3 (D)
unnamed: Q11.1 (G), R11.2, R13.2
unnamed: Q12.1 (G), R12.2, R14.2
unnamed: Q21.1 (G), R21.2, R23.2
unnamed: Q22.1 (G), R22.2, R24.2
unnamed: Q31.1 (G), R31.2, R33.2
unnamed: Q32.1 (G), R32.2, R34.2
unnamed: Q41.1 (G), R41.2, R43.2
unnamed: Q42.1 (G), R42.2, R44.2
unnamed: Q51.1 (G), R51.2, R53.2
unnamed: Q52.1 (G), R52.2, R54.2
unnamed: Q61.1 (G), R61.2, R63.2
unnamed: Q62.1 (G), R62.2, R64.2
unnamed: Q71.1 (G), R71.2, R73.2
unnamed: Q72.1 (G), R72.2, R74.2
unnamed: Q81.1 (G), R81.2, R83.2
unnamed: Q82.1 (G), R82.2, R84.2
unnamed: SW1.1 (A), U1.12 (PB0)
unnamed: R3.2, U3.7 (EN)
